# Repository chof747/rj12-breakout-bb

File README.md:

## RJ12 Breakout Board for Breadboards

This is a breakout board to be able to use RJ12 sockets with four pins (pin 2,3,4,5 connected) on a breadboard.

## Revision History:

- **v1.0**: Initial version (Produced: 15.10.2023)

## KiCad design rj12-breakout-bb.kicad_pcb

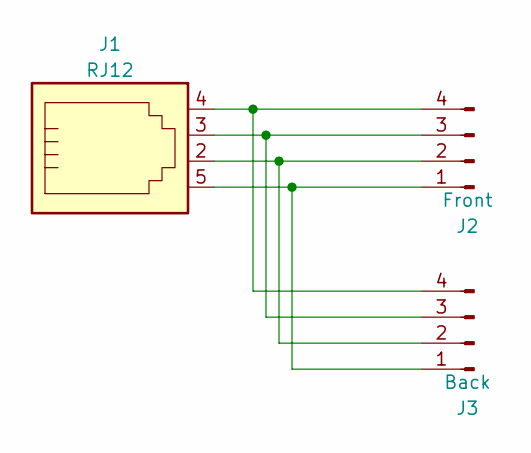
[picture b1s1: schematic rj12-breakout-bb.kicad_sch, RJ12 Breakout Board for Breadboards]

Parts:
J1: RJ12; RJ12_Amphenol_54601
J2: Front; PinHeader_1x04_P2.54mm_Vertical
J3: Back; PinHeader_1x04_P2.54mm_Vertical

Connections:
unnamed: J1.5, J2.1, J3.1
unnamed: J1.2, J2.2, J3.2
unnamed: J1.3, J2.3, J3.3
unnamed: J1.4, J2.4, J3.4

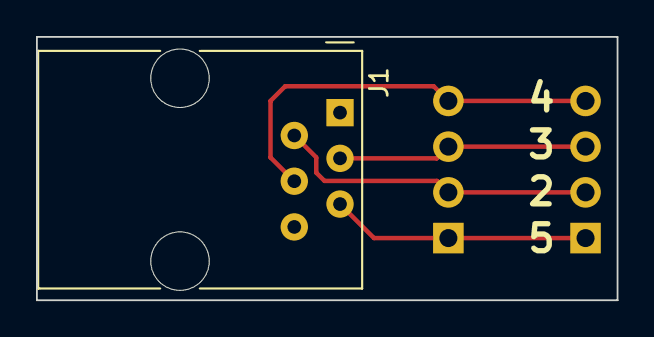
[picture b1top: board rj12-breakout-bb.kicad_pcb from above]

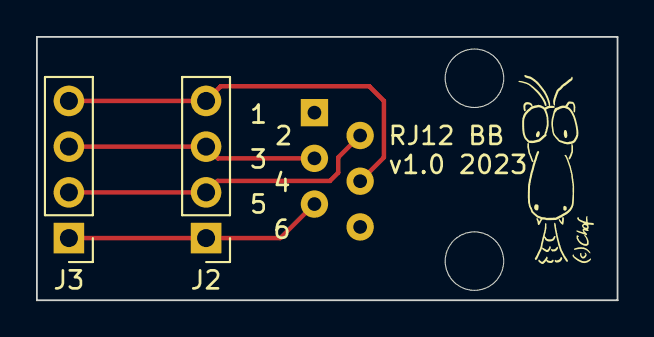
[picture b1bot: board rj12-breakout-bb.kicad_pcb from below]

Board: 2 copper layers, 32.3 x 14.6 mm, 3 parts (2 on the bottom side), 4 nets.

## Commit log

2023-09-28 Initialized kiCad project to correct name
2023-09-30 Initial version
2023-10-15 Ordered Version 1.0
2023-10-15 Corrected readme
